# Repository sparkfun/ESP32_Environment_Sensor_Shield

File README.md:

SparkFun ESP32 Environment Sensor Shield
========================================

[*SparkFun ESP32 Thing Environment Sensor Shield (DEV-14153)*](https://www.sparkfun.com/products/14153)

The SparkFun ESP32 Thing Environment Sensor Shield provides sensors and hookups for monitoring environmental conditions. While incorporating three sensors capable of measuring five different environmental variables as well as providing connections for several other sensors, this sensor shield creates the best way to make your ESP32 Thing more accurate than your local weatherman!

Repository Contents
-------------------

* **/Documentation** - Data sheets, additional product information
* **/Firmware** - Example code 
* **/Hardware** - Eagle design files (.brd, .sch)
* **/Production** - Production panel files (.brd)

Version History
---------------
* [v_H1.0](https://github.com/sparkfun/ESP32_Environment_Sensor_Shield/tree/v_H1.0) - Initial release

License Information
-------------------

This product is _**open source**_! 

Please review the LICENSE.md file for license information. 

If you have any questions or concerns on licensing, please contact techsupport@sparkfun.com.

Distributed as-is; no warranty is given.

- Your friends at SparkFun.

_<COLLABORATION CREDIT>_

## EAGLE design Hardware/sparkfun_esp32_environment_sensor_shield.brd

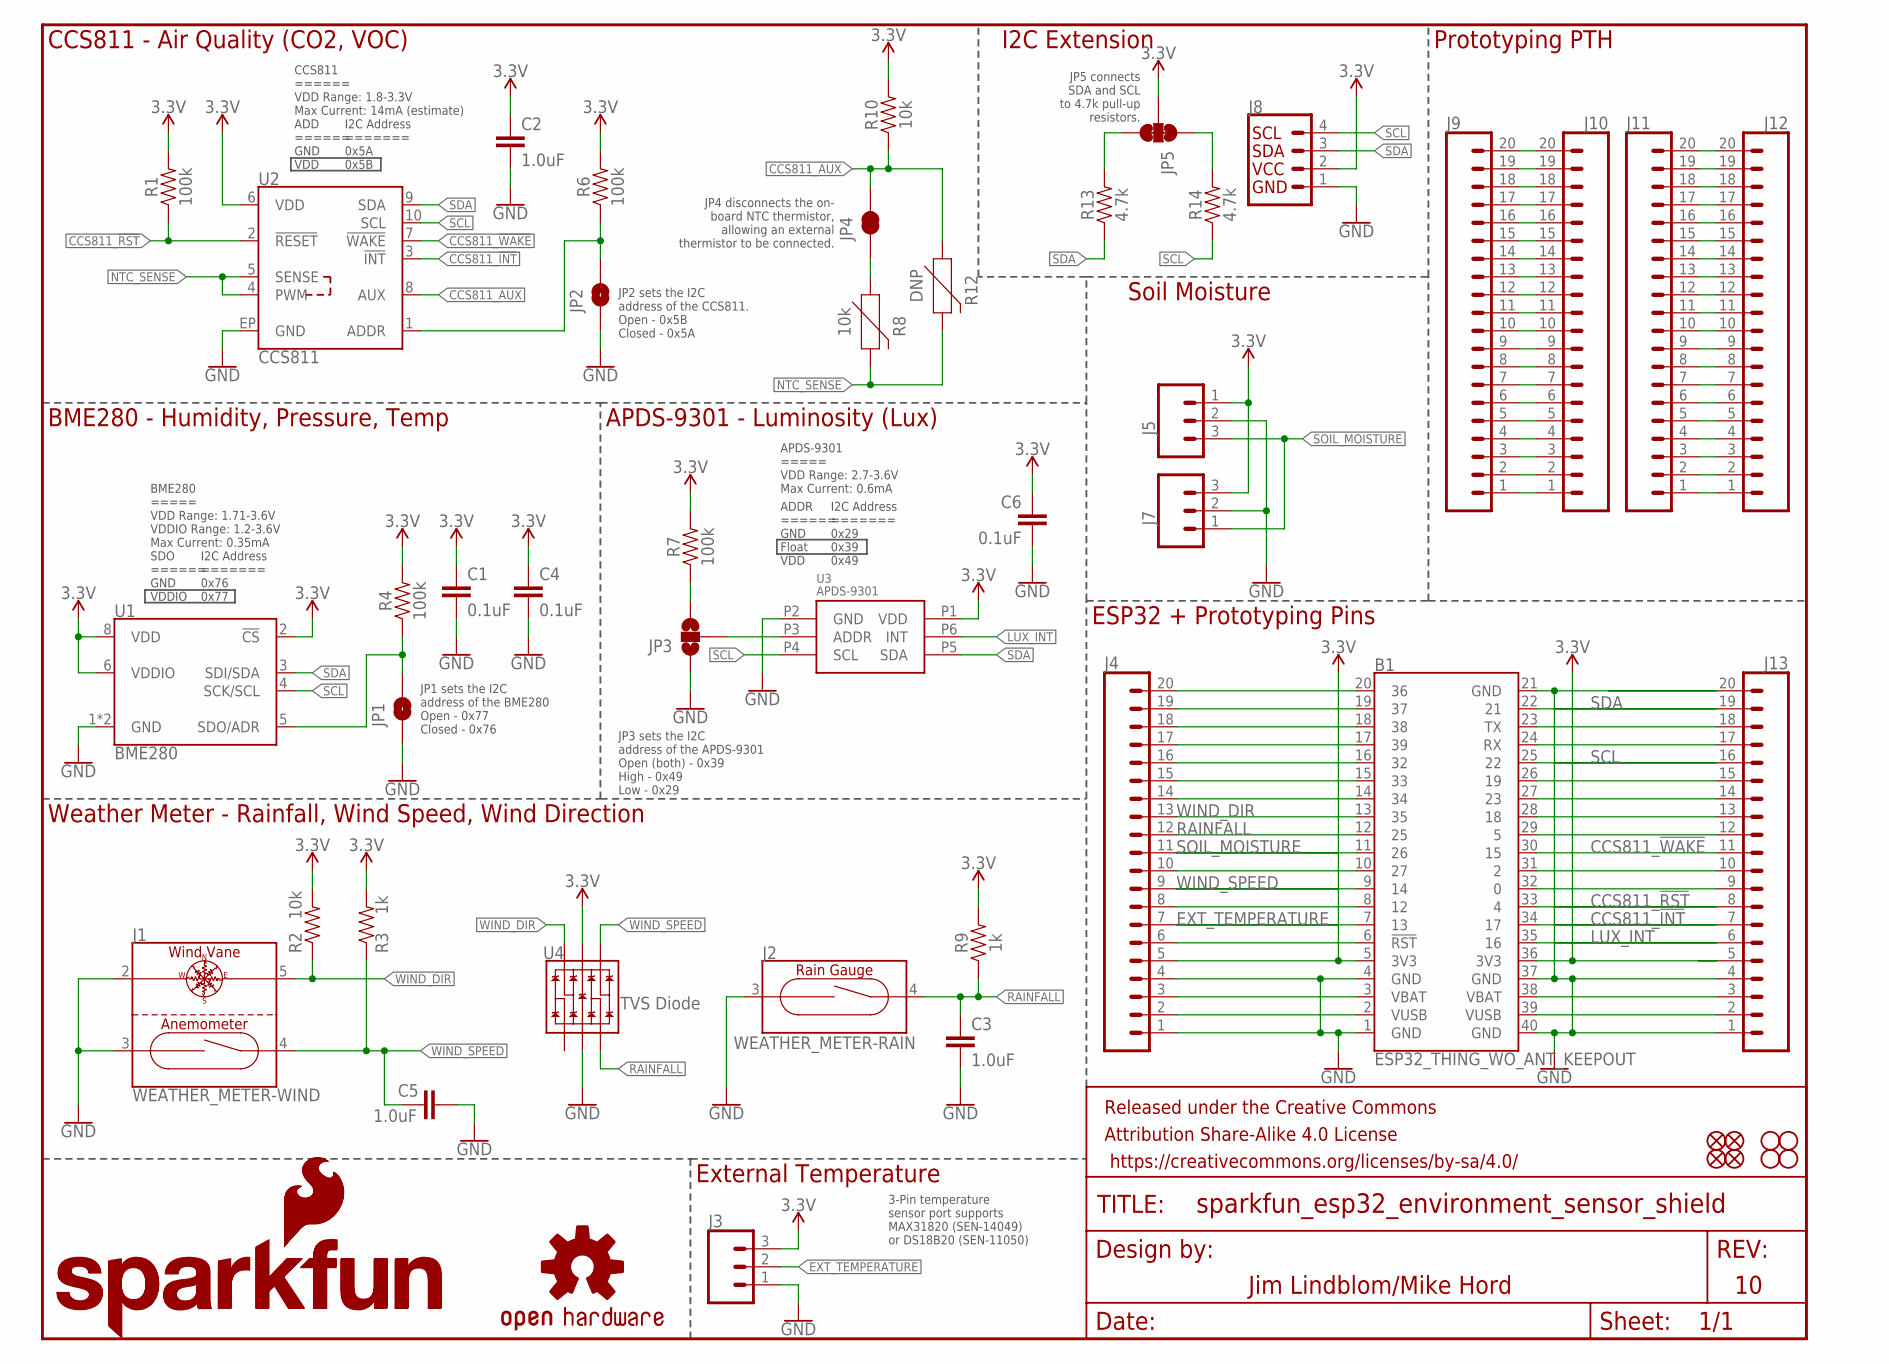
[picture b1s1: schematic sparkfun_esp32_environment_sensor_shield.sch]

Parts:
B1: ESP32_THING_WO_ANT_KEEPOUT; ESP32_THING_NO_ANT
C1, C4, C6: 0.1uF; 0603
C2, C3, C5: 1.0uF; 0603
FD1, FD2, FD3, FD4: FIDUCIAL1X2; FIDUCIAL-1X2
FRAME1: FRAME-LETTER; CREATIVE_COMMONS
H1, H2, H3, H4: STAND-OFF
J1: WEATHER_METER-WIND; RJ11-6
J2: WEATHER_METER-RAIN; RJ11-6
J3, J5: CONN_03; 1X03
J4, J9, J10, J11, J12, J13: CONN_20NOSILK; 1X20_NOSILK
J7: CONN_03SCREW-NS; SCREWTERMINAL-3.5MM-3-NS
J8: I2C_STANDARD; 1X04
JP1, JP2: JUMPER-SMT_2_NO_SILK; SMT-JUMPER_2_NO_SILK
JP3: JUMPER-SMT_3_NO_SILK; SMT-JUMPER_3_NO_SILK
JP4: JUMPER-SMT_2_NC_TRACE_SILK; SMT-JUMPER_2_NC_TRACE_SILK
JP5: JUMPER-SMT_3_2-NC_TRACE_SILK; SMT-JUMPER_3_2-NC_TRACE_SILK
LOGO1: SFE_LOGO_NAME.1_INCH; SFE_LOGO_NAME_.1
LOGO2: SFE_LOGO_NAME_FLAME.1_INCH; SFE_LOGO_NAME_FLAME_.1
LOGO3: SFE_LOGO_FLAME.1_INCH; SFE_LOGO_FLAME_.1
LOGO4: OSHW-LOGOS; OSHW-LOGO-S
R1, R4, R6, R7: 100k; 0603
R2, R8, R10: 10k; 0603
R3, R9: 1k; 0603
R12: DNP; AXIAL-0.1
R13, R14: 4.7k; 0603
U1: BME280; LGA-8-2.5X2.5
U2: CCS811; LGA10-2.7X4.0MM
U3: APDS-9301; CHIPLED-6
U4: TVS Diode; SOT-23-6

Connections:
3.3V: B1.5 (3V3), B1.36 (3V3), C1.1, C2.1, C4.1, C6.1, J3.3, J4.5, J5.1, J7.3, J8.2, J13.5, JP5.2, R1.2, R2.2, R3.2, R4.2, R6.2, R7.2, R9.2, R10.2, U1.2 (!CS), U1.6 (VDDIO), U1.8 (VDD), U2.6 (VDD), U3.P1 (VDD), U4.5 (VCC)
ADDR_TSL2561: JP3.2, U3.P3 (ADDR)
CCS811_!INT!: B1.34 (17), J13.7, U2.3 (!INT!)
CCS811_!RST!: B1.33 (4), J13.8, R1.1, U2.2 (!RESET!)
CCS811_!WAKE!: B1.30 (15), J13.11, U2.7 (!WAKE!)
CCS811_ADDR: JP2.2, R6.1, U2.1 (ADDR)
CCS811_AUX: JP4.2, R10.1, R12.P$1 (1), U2.8 (AUX)
EXT_TEMPERATURE: B1.7 (13), J3.2, J4.7
GND: B1.1 (GND), B1.4 (GND), B1.21 (GND), B1.37 (GND), B1.40 (GND), C1.2, C2.2, C3.2, C4.2, C5.2, C6.2, J1.2 (DIR-1), J1.3 (ANN-1), J2.3 (1), J3.1, J4.1, J4.4, J5.2, J7.2, J8.1, J13.1, J13.4, J13.20, JP1.1, JP2.1, JP3.1, U1.1 (GND), U1.7 (GND), U2.EP (GND), U3.P2 (GND), U4.2 (VSS)
LUX_INT: B1.35 (16), J13.6, U3.P6 (INT)
unnamed: JP3.3, R7.1
unnamed: JP1.2, R4.1, U1.5 (SDO/ADR)
unnamed: JP4.1, R8.1
unnamed: JP5.3, R13.2
unnamed: JP5.1, R14.2
unnamed: B1.2 (VUSB), J4.2
unnamed: B1.3 (VBAT), J4.3
unnamed: B1.6 (!RST!), J4.6
unnamed: B1.10 (27), J4.10
unnamed: B1.14 (34), J4.14
unnamed: B1.15 (33), J4.15
unnamed: B1.16 (32), J4.16
unnamed: B1.17 (39), J4.17
unnamed: B1.18 (38), J4.18
unnamed: B1.19 (37), J4.19
unnamed: B1.20 (36), J4.20
unnamed: B1.39 (VUSB), J13.2
unnamed: B1.38 (VBAT), J13.3
unnamed: B1.32 (0), J13.9
unnamed: B1.31 (2), J13.10
unnamed: B1.8 (12), J4.8
unnamed: B1.29 (5), J13.12
unnamed: B1.28 (18), J13.13
unnamed: B1.27 (23), J13.14
unnamed: B1.26 (19), J13.15
unnamed: B1.24 (RX), J13.17
unnamed: B1.23 (TX), J13.18
unnamed: J11.1, J12.1
unnamed: J11.2, J12.2
unnamed: J11.3, J12.3
unnamed: J11.4, J12.4
unnamed: J11.5, J12.5
unnamed: J11.6, J12.6
unnamed: J11.7, J12.7
unnamed: J11.8, J12.8
unnamed: J11.9, J12.9
unnamed: J11.10, J12.10
unnamed: J11.11, J12.11
unnamed: J11.12, J12.12
unnamed: J11.13, J12.13
unnamed: J11.14, J12.14
unnamed: J11.15, J12.15
unnamed: J11.16, J12.16
unnamed: J11.17, J12.17
unnamed: J11.18, J12.18
unnamed: J11.19, J12.19
unnamed: J11.20, J12.20
unnamed: J9.1, J10.1
unnamed: J9.2, J10.2
unnamed: J9.3, J10.3
unnamed: J9.4, J10.4
unnamed: J9.5, J10.5
unnamed: J9.6, J10.6
unnamed: J9.7, J10.7
unnamed: J9.8, J10.8
unnamed: J9.9, J10.9
unnamed: J9.10, J10.10
unnamed: J9.11, J10.11
unnamed: J9.12, J10.12
unnamed: J9.13, J10.13
unnamed: J9.14, J10.14
unnamed: J9.15, J10.15
unnamed: J9.16, J10.16
unnamed: J9.17, J10.17
unnamed: J9.18, J10.18
unnamed: J9.19, J10.19
unnamed: J9.20, J10.20
NTC_SENSE: R8.2, R12.P$2 (2), U2.4 (PWM), U2.5 (SENSE)
RAINFALL: B1.12 (25), C3.1, J2.4 (2), J4.12, R9.1, U4.3 (IO2)
SCL: B1.25 (22), J8.4, J13.16, R14.1, U1.4 (SCK/SCL), U2.10 (SCL), U3.P4 (SCL)
SDA: B1.22 (21), J8.3, J13.19, R13.1, U1.3 (SDI/SDA), U2.9 (SDA), U3.P5 (SDA)
SOIL_MOISTURE: B1.11 (26), J4.11, J5.3, J7.1
WIND_DIR: B1.13 (35), J1.5 (DIR2), J4.13, R2.1, U4.6 (IO4)
WIND_SPEED: B1.9 (14), C5.1, J1.4 (ANN-2), J4.9, R3.1, U4.4 (IO3)

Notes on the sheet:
APDS-9301 ===== VDD Range: 2.7-3.6V Max Current: 0.6mA
ADDR ====== GND Float VDD
I2C Address ======= 0x29 0x39 0x49
BME280 ===== VDD Range: 1.71-3.6V VDDIO Range: 1.2-3.6V Max Current: 0.35mA
SDO ====== GND VDDIO
I2C Address ======= 0x76 0x77
CCS811 ====== VDD Range: 1.8-3.3V Max Current: 14mA (estimate)
ADD ====== GND VDD
I2C Address ======= 0x5A 0x5B
CCS811 - Air Quality (CO2, VOC)
BME280 - Humidity, Pressure, Temp
APDS-9301 - Luminosity (Lux)
Weather Meter - Rainfall, Wind Speed, Wind Direction
I2C Extension
Soil Moisture
Prototyping PTH
ESP32 + Prototyping Pins
External Temperature
JP2 sets the I2C address of the CCS811. Open - 0x5B Closed - 0x5A
JP1 sets the I2C address of the BME280 Open - 0x77 Closed - 0x76
JP3 sets the I2C address of the APDS-9301 Open (both) - 0x39 High - 0x49 Low - 0x29
JP4 disconnects the on- board NTC thermistor, allowing an external thermistor to be connected.
JP5 connects SDA and SCL to 4.7k pull-up resistors.
Jim Lindblom/Mike Hord
3-Pin temperature sensor port supports MAX31820 (SEN-14049) or DS18B20 (SEN-11050)

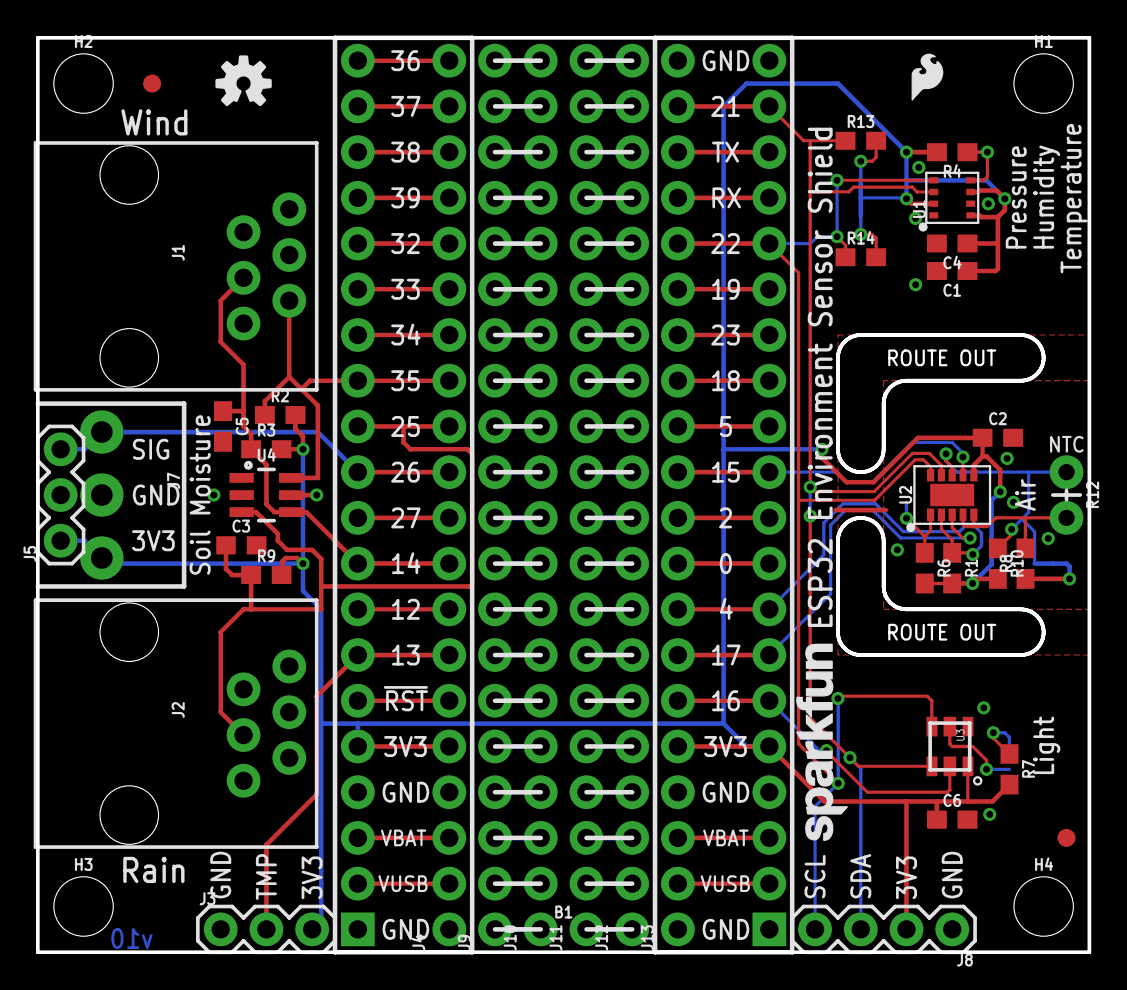
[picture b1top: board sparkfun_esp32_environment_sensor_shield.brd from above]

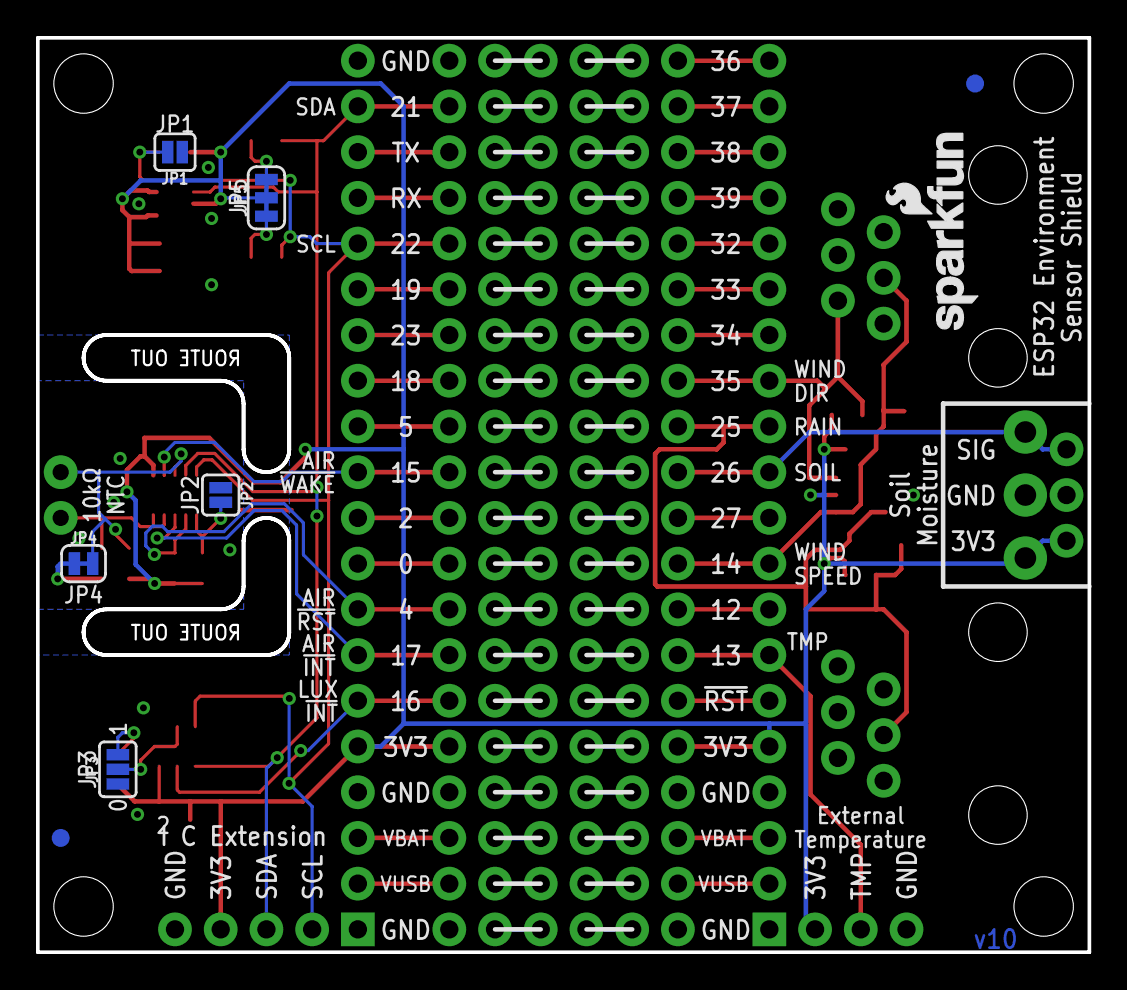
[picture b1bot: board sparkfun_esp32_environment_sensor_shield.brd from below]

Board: 2 copper layers, 58.4 x 50.8 mm, 53 parts (8 on the bottom side), 84 nets.

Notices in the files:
parts and their libraries:
SparkFun-Boards: Licensing: Creative Commons ShareAlike 4.0 International - https://creativecommons.org/licenses/by-sa/4.0
SparkFun-Aesthetics: Released under the Creative Commons Attribution Share-Alike 4.0 License
SparkFun-Aesthetics: https://creativecommons.org/licenses/by-sa/4.0
